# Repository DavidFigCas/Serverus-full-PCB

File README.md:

# Serverus-full-PCB
Archivos del diseño electrónico de la tarjeta PCB de Serverus Full (RPi Zero)

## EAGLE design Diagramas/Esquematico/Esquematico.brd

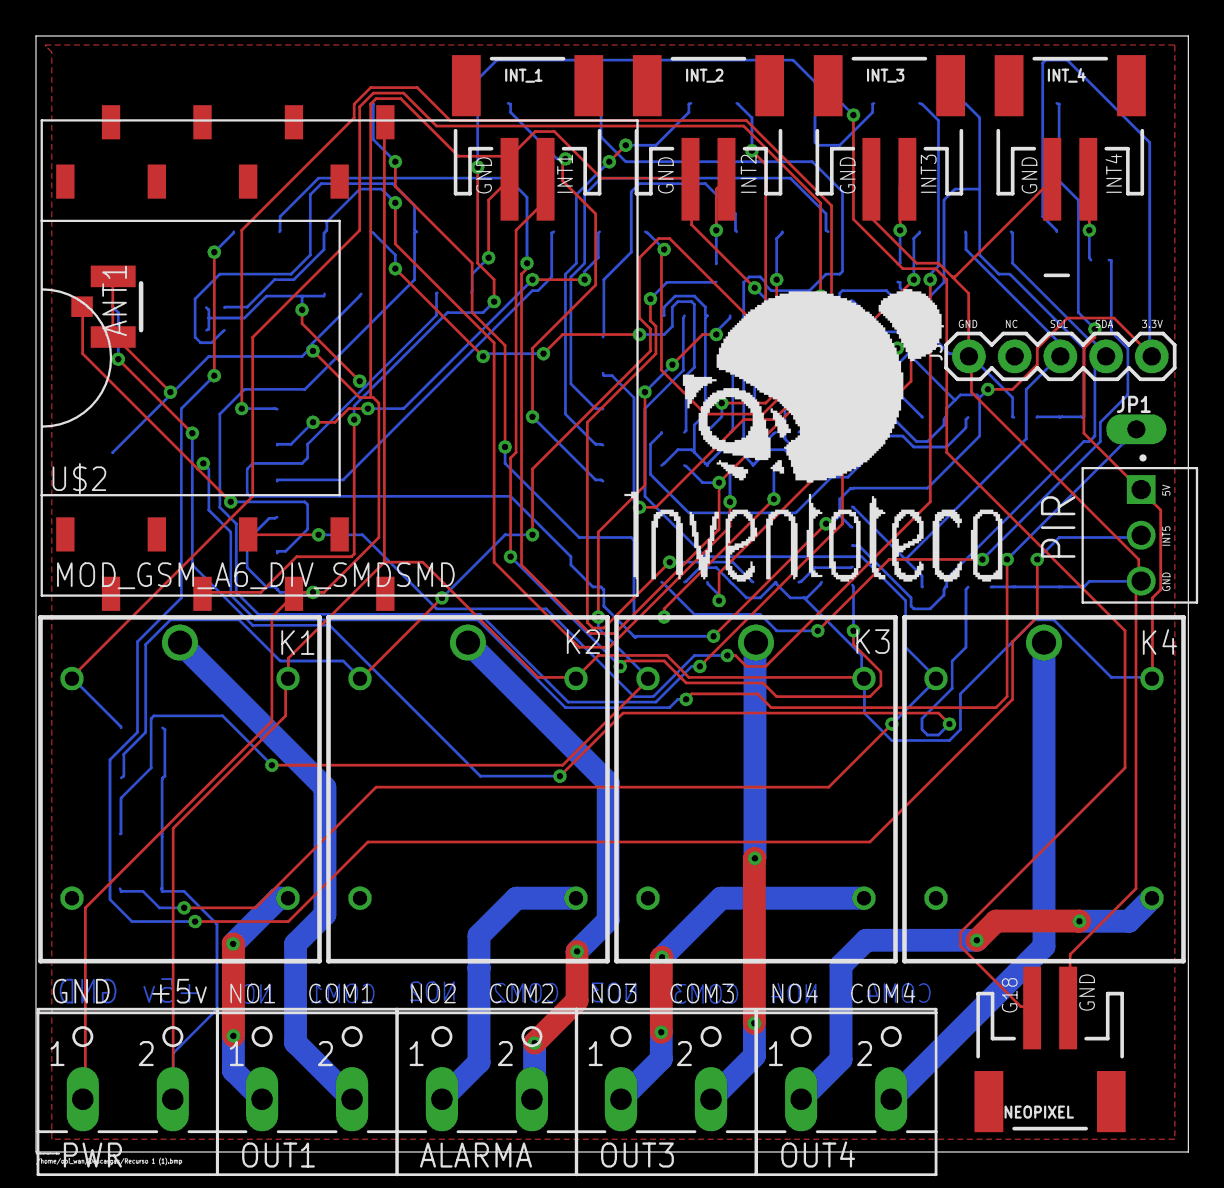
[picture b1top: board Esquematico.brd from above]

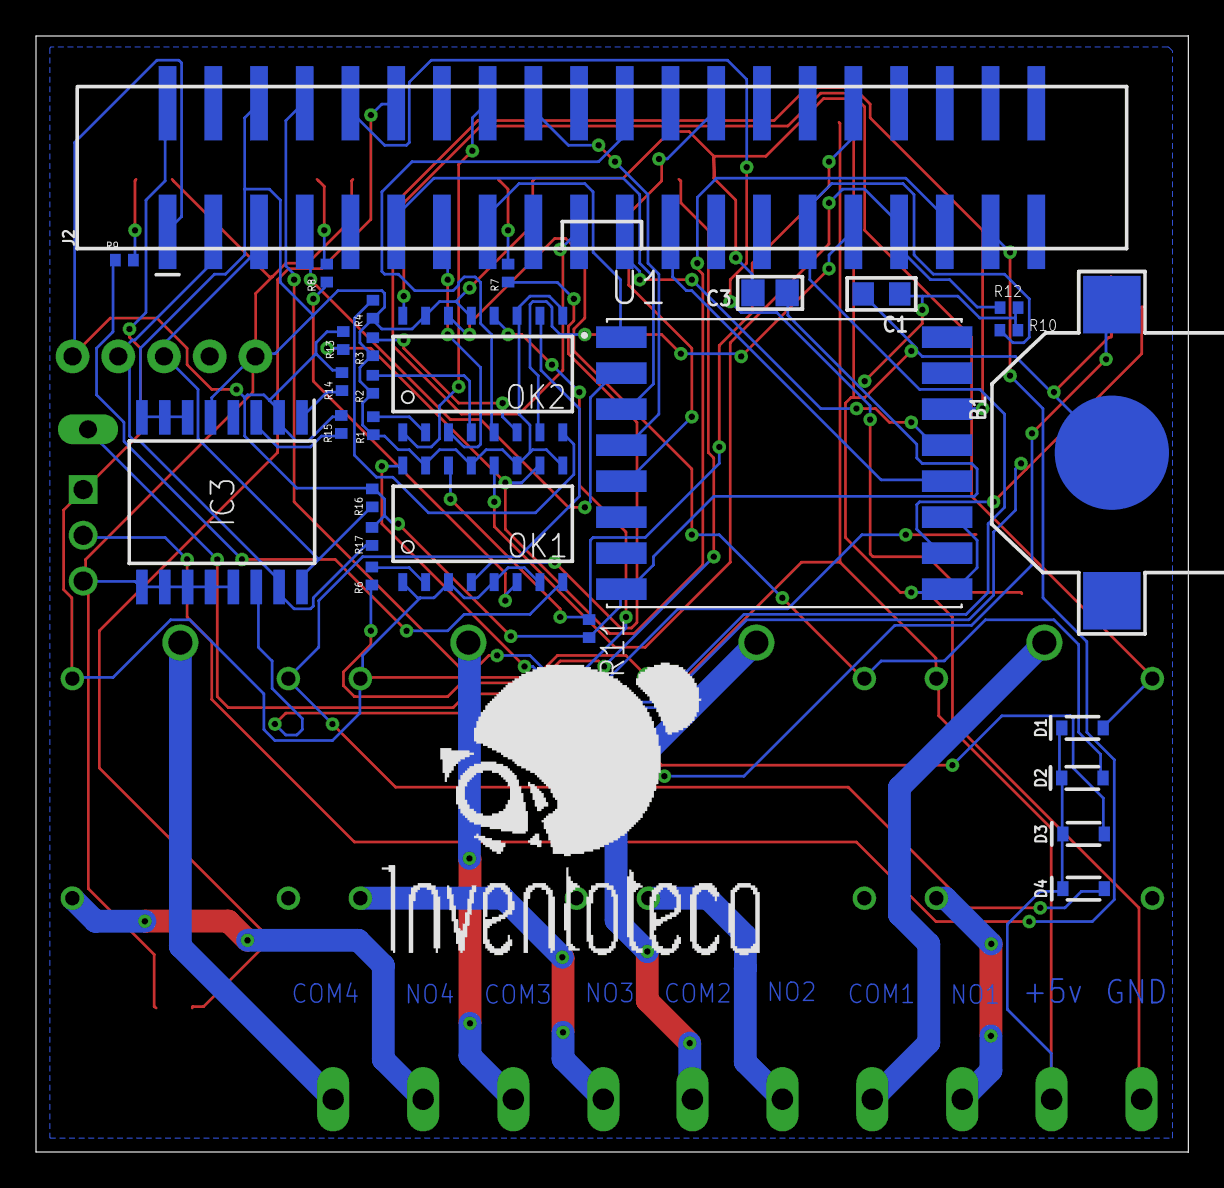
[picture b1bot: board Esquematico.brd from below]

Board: 2 copper layers, 64.0 x 62.0 mm, 47 parts (28 on the bottom side), 53 nets.

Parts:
ALARMA: W237-102
ANT1: RECE.20279.001E.01
B1: CR1220
C1: 0.1F; _0805
C3: 0805_NOTHERMALS
D1, D2, D3, D4: 250mA/100V; SOD-323
IC3: DS3231N_DIP; SOIC127P1032X265-16N
INT_1, INT_2, INT_3, INT_4: JST-2-SMD
J2: RASPBERRYPI-40-PIN-GPIO_SMT; 2X20_SHROUDED_SMT
J3: 1X05
JP1: 1X01_OVAL
K1, K2, K3, K4: SRD-05VDC-SL-C; SRD
NEOPIXEL: JST-2-SMD
OK1, OK2: TLP283-4; MINI-FLAT-16
OUT1, OUT3, OUT4: W237-102
PIR: 22-11-2032; MOLEX_22-11-2032
PWR: W237-102
R1, R2, R3, R4, R6, R7, R8, R9: 220; R0402
R10, R11, R12, R13: 1k; R0402
R14, R15, R16, R17: 10K; R0402
U1: RFM69HW-868S2; XCVR_RFM69HW-868S2
U$2: MOD_GSM_A6_DIV_SMDSMD; MOD_GSM_A6_SDM

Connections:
3.3V: C1.1, C3.1, IC3.2, J2.1, J3.5, R10.2, R11.2, R12.2, R13.2, R14.2, R15.2, R16.2, R17.2, U1.8
5V: D1.C, D2.C, D3.C, D4.C, J2.2, K1.2, K2.2, K3.2, K4.2, OK1.1, OK1.3, OK1.5, OK1.7, PIR.1, PWR.2, U$2.VCC
ANT_LORA: ANT1.3, JP1.1, U1.10
COM1: K1.1, OUT1.2
COM2: ALARMA.2, K2.1
COM3: K3.1, OUT3.2
COM4: K4.1, OUT4.2
G0: J2.7, U1.2
G1: J2.11, U1.3
G2: J2.18, U1.4
G3: J2.26, U1.5
G18: J2.12, NEOPIXEL.2
GND: ANT1.1, ANT1.2, B1.-, C1.2, C3.2, IC3.5, IC3.6, IC3.7, IC3.8, IC3.9, IC3.10, IC3.11, IC3.12, IC3.13, INT_1.1, INT_2.1, INT_3.1, INT_4.1, J2.6, J3.1, NEOPIXEL.1, OK1.9, OK1.11, OK1.13, OK1.15, OK2.9, OK2.11, OK2.13, OK2.15, PIR.3, PWR.1, R1.1, R2.1, R3.1, R4.1, U1.9, U1.11, U$2.GND
INT1: J2.29, OK1.16, R10.1
INT2: J2.32, OK1.14, R11.1
INT3: J2.33, OK1.12, R12.1
INT4: J2.35, OK1.10, R13.1
INT5: J2.37, PIR.2
MISO: J2.21, U1.13
MOSI: J2.19, U1.14
unnamed: IC3.1, R14.1
unnamed: INT_1.2, R6.1
unnamed: OK1.2, R6.2
unnamed: INT_2.2, R7.1
unnamed: OK2.2, R1.2
unnamed: OK2.4, R2.2
unnamed: OK2.6, R3.2
unnamed: OK2.8, R4.2
unnamed: OK1.4, R7.2
unnamed: OK1.6, R8.1
unnamed: INT_3.2, R8.2
unnamed: OK1.8, R9.1
unnamed: INT_4.2, R9.2
unnamed: D4.A, K4.3, OK2.10
unnamed: D3.A, K3.3, OK2.12
unnamed: D2.A, K2.3, OK2.14
unnamed: D1.A, K1.3, OK2.16
NO1: K1.4, OUT1.1
NO2: ALARMA.1, K2.4
NO3: K3.4, OUT3.1
NO4: K4.4, OUT4.1
OUT1: J2.16, OK2.1
OUT3: J2.22, OK2.5
OUT4: J2.31, OK2.7
OUT_ALARMA: J2.13, OK2.3
RST_LORA: J2.15, U1.1
SCK: J2.23, U1.12
SCL: IC3.16, J2.5, J3.3, R16.1
SDA: IC3.15, J2.3, J3.4, R17.1
SQW: IC3.3, R15.1
URX: J2.8, U$2.URX
UTX: J2.10, U$2.UTX
VBAT: B1.+$1, IC3.14

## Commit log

2020-01-06 Borrador del diagrama esquemático
    Requerimientos de entradas y salidas, pines para comunicación
2020-01-07 movi el pir
    movi el pir
2020-01-07 Coenexion de relevadores
    Relevadores conectados
2020-01-07 Conexion de las entradas
    Entradas optoacopladas
2020-01-07 cambio de lugar de la raspberry
2020-01-07 Lora PCB
    Esquematico y Pcb
2020-01-07 imagen de lora
2020-01-08 Cambio de la fuente
    se quito la fuente propuesta
2020-01-08 conexion Lora
    conexion del modulo lora
2020-01-08 modulo gsm
2020-01-09 cambio de lugar de lora
2020-01-09 imagenes
2020-01-10 Libreria Gsm a6
    Creaciòn de la librería del módulo GSM_A6
2020-01-10 Imagen de conexión modulo lora
2020-01-10 Castelado Lora
    Conexion dell castelado de lora
2020-01-10 Conexion
    Conexion del catelado Lora
2020-01-10 Ceacion del pcb
2020-01-11 Medicion del SIM808
2020-01-12 modulo smd
    modulos lors y gsm en smd
2020-01-12 modulo lora
2020-01-13 Modulos en smd
2020-01-13 Acomo de coponentes
2020-01-14 Ruteado de los componentes
2020-01-14 imagenes pcb
2020-01-15 islas terminadas
2020-01-15 Pcb con Smd
2020-01-15 Cambio
2020-01-15 Modulo Lora Eliminado
2020-01-15 Sustitucion de la Bateria
    Cambio de la bateria CR2032 por CR1220
2020-01-15 Pcb "Terminado"
2020-01-16 Modificaciòn del tamaño de la pcb
2020-01-16 Imagen Rtc mini
2020-01-16 Cambio de lugar entradas
2020-01-16 Cambio de lugar
2020-01-16 Cambio de lugar de la pila
2020-01-16 sensor pir mini
2020-01-17 Logo Inventoteca
2020-01-17 Etiquetas del sensor pir
2020-01-17 Cambio de lugar de las etiquetas en la salidas
2020-01-17 LOGOS

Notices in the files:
parts and their libraries:
microbuilder: This work is placed in the public domain, and may be freely used for commercial and non-commercial work with the following conditions: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
SparkFun-DiscreteSemi: Licensing: Creative Commons ShareAlike 4.0 International - https://creativecommons.org/licenses/by-sa/4.0
